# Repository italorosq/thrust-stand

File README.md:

# thrust-stand

## 📋 Sobre

Sistema embarcado baseado em ESP32 para monitoramento de testes estáticos de motores de foguetes, com aquisição de dados de empuxo e pressão em tempo real, armazenamento em cartão SD e comunicação via Serial/Bluetooth.

## 🚀 Quick Start

1. Clone o repositório

```bash
git clone https://github.com/ViniciusCMB/thrust-stand.git
```

2. Configure o hardware conforme [esquemático](./docs/HARDWARE.md)
3. Carregue o firmware

## 📁 Estrutura do Projeto

```
├── 📂 docs/              # Documentação técnica detalhada
├── 📂 extras/            # Códigos extras utilizados
├── 📂 firmware/          # Código do microcontrolador ESP32
├── 📂 hardware/          # Esquemáticos, PCBs e lista de componentes
├── 📂 software/          # Ferramentas de análise e interface
└── 📂 tests/             # Testes unitários e de integração
```

## 🔧 Pré-requisitos

- Hardware: ESP32 DevKit V1, célula de carga + HX711, sensor de pressão (com divisor resistivo), módulo microSD (SPI), 2 botões tácteis (`GPIO32` para TARE e `GPIO33` para novo arquivo), LED com resistor de limitação
- Software: Arduino IDE 2.0+
- Bibliotecas: ver `docs/FIRMWARE.md`

## 📖 Documentação

- [Esquemático e Montagem](./docs/HARDWARE.md)
- [Firmware e Arquitetura](./docs/FIRMWARE.md)
- [Protocolos e API](./docs/API.md)
- [Troubleshooting](./docs/TROUBLESHOOTING.md)

## 🎯 Funcionalidades

- ✅ Aquisição de dados de empuxo e pressão em tempo real
- ✅ Armazenamento em cartão SD com arquivos sequenciais
- ✅ Controle local por botões (TARE e novo arquivo)
- ✅ LED de status de gravação no SD
- ✅ Comunicação (Serial, Bluetooth)
- ✅ Calibração persistente da célula de carga

## 📊 Dados de Teste

Os dados de testes estáticos de motores específicos são armazenados no repositório dedicado:
[motor](https://github.com/Serra-Rocketry/motor)

Este repositório (thrust-stand) contém apenas o sistema de aquisição. Os dados coletados durante os testes devem ser commitados no repositório `motor`.

## 🤝 Contribuindo

Este projeto segue as [Boas Práticas da Serra Rocketry](https://github.com/Serra-Rocketry/best-practices). Para contribuir:

1. Fork o projeto
2. Crie uma branch para sua feature (`git checkout -b feature/AmazingFeature`)
3. Commit suas mudanças (`git commit -m 'Add some AmazingFeature'`)
4. Push para a branch (`git push origin feature/AmazingFeature`)
5. Abra um Pull Request

## ✨ Autores

- Equipe Serra Rocketry - Desenvolvimento e documentação
- Contribuidores - [Lista de contribuidores]()

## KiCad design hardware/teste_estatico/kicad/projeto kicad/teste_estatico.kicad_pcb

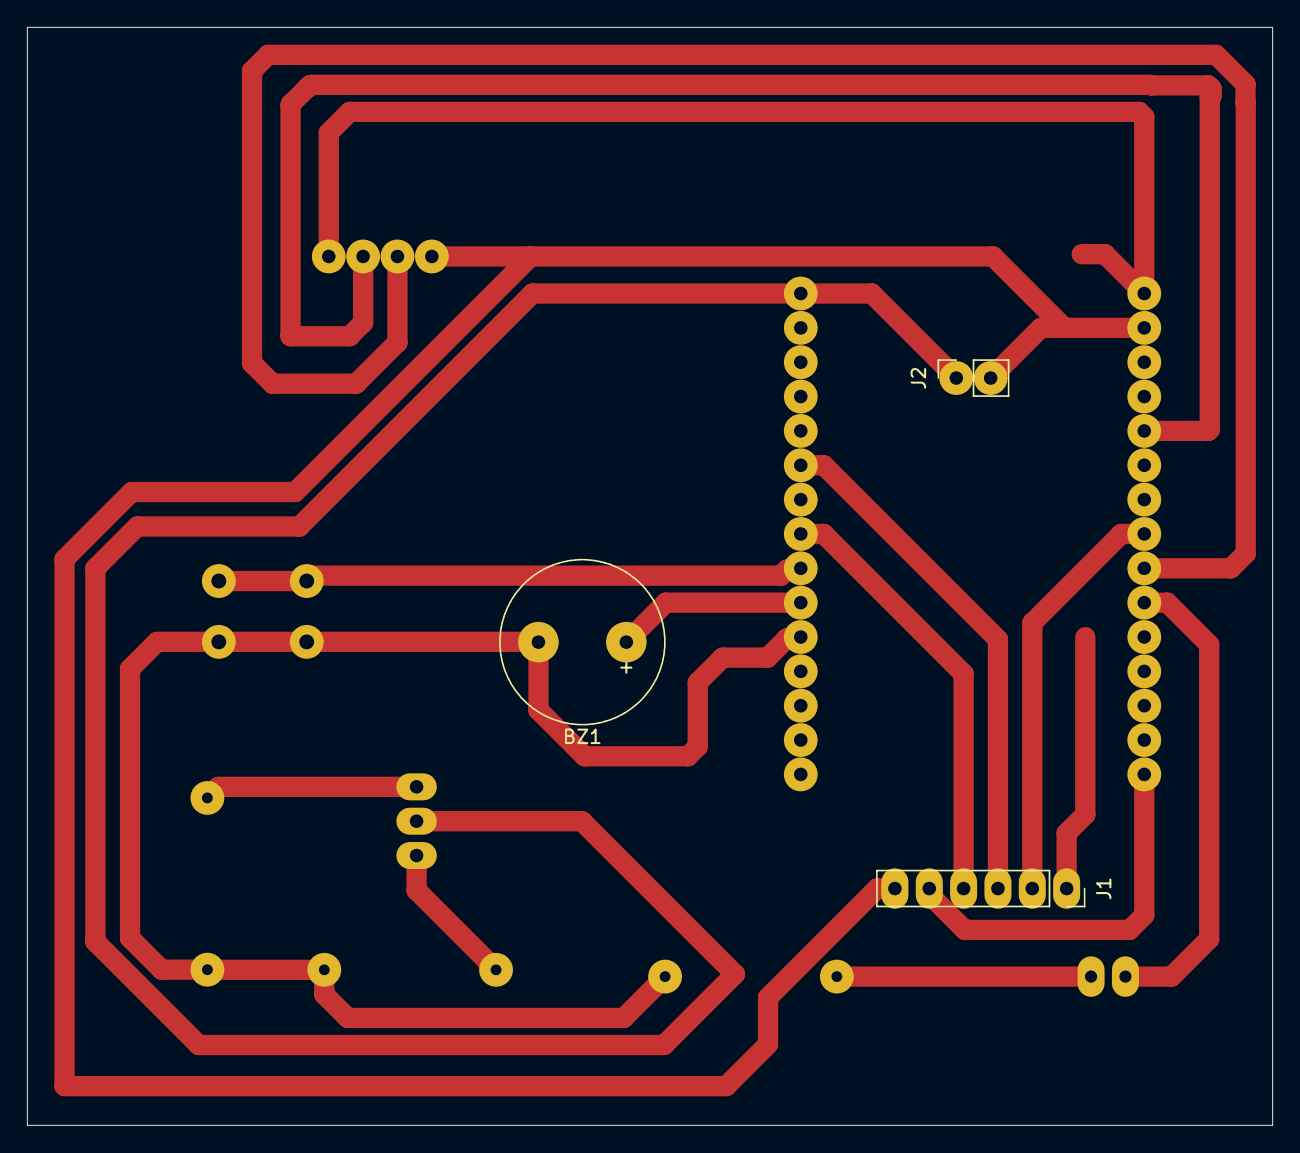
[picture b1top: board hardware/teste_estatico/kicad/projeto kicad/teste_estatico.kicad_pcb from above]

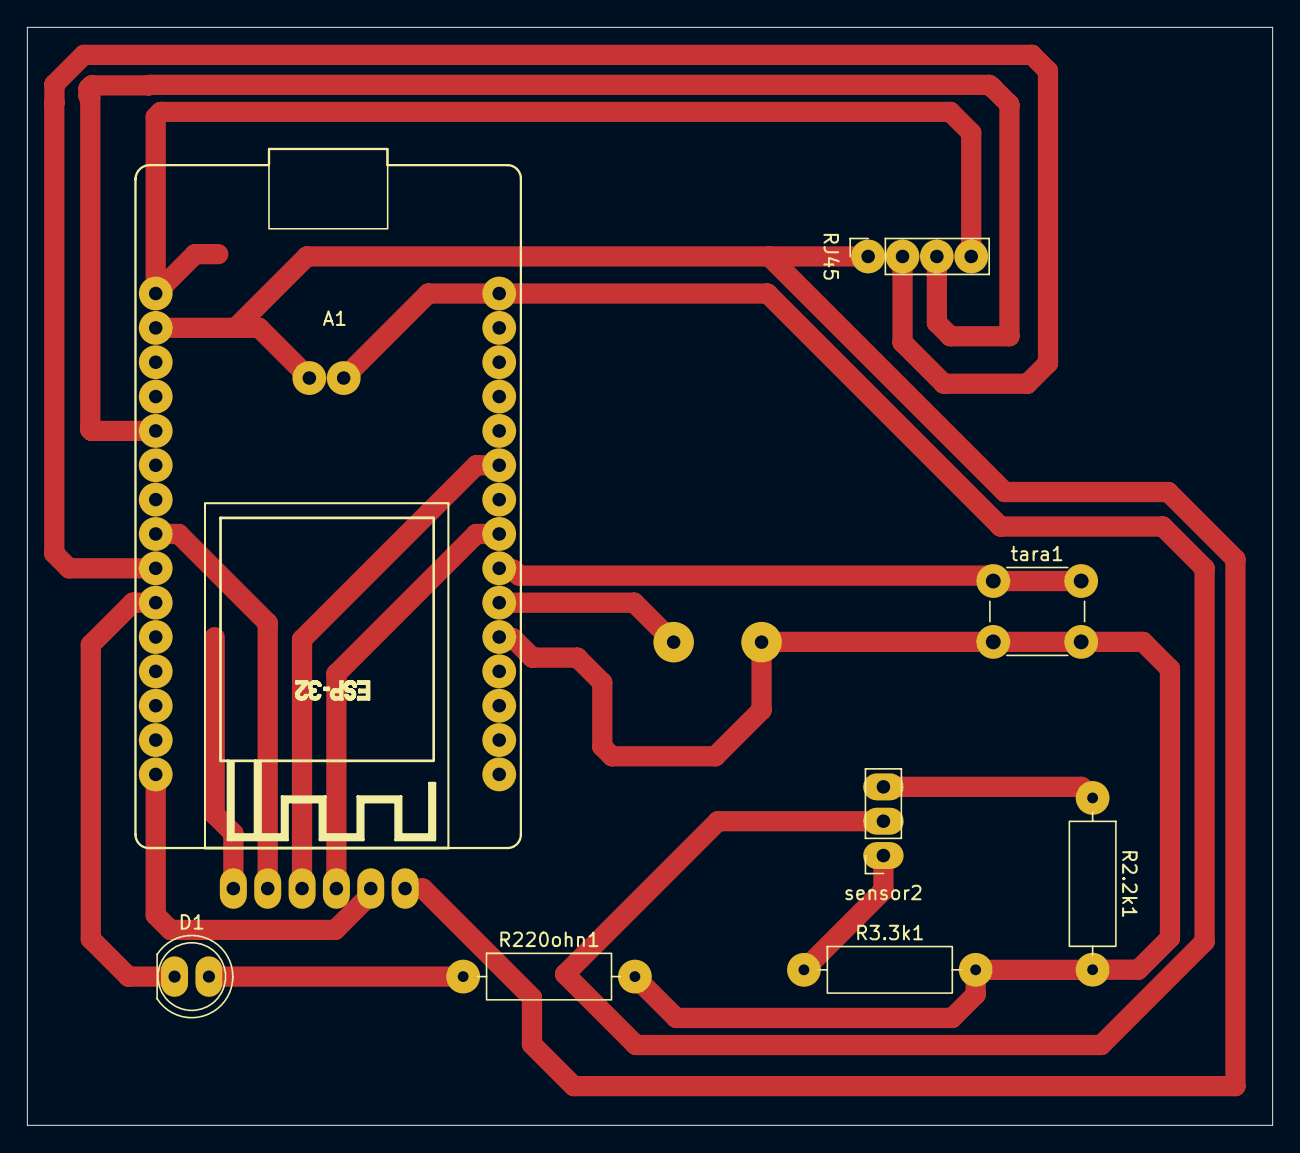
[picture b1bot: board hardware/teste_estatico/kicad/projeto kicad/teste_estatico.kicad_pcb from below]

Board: 2 copper layers, 92.1 x 81.2 mm, 11 parts (8 on the bottom side), 16 nets.

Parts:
A1: ESP32_DevKit_V1_DOIT_30GPIOs; DOIT_ESP32_DEVKIT_30Pins
BZ1: Buzzer_5V; MagneticBuzzer_ProSignal_ABT-410-RC
D1: LED; LED_D5.0mm_FlatTop
J1: PINHD_1x6_Female; PinSocket_1x06_P2.54mm_Vertical
J2: PINHD_1x2_Female; PinSocket_1x02_P2.54mm_Vertical
R2.2k1, R3.3k1, R220ohn1: R; R_Axial_DIN0309_L9.0mm_D3.2mm_P12.70mm_Horizontal
RJ45: conexão do rj45; PinSocket_1x04_P2.54mm_Vertical
sensor2: Sensor de pressão; PinSocket_1x03_P2.54mm_Vertical
tara1: Push_Button; SW_PUSH_6mm

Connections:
3.3V: A1.1 (3.3V), J1.1, RJ45.4
GND: A1.2 (GND), J1.6, J2.2, RJ45.1
unnamed: A1.21 (ADC1_CH4/D32), BZ1.1
unnamed: A1.22 (ADC1_CH4/D32), tara1.1
unnamed: A1.20 (ADC1_CH7/D35), A1.29 (GND), BZ1.2, R2.2k1.2, R3.3k1.2, R220ohn1.2, tara1.2
unnamed: A1.25 (ADC2_CH7/D27), J1.3
unnamed: A1.5 (D4/ADC2_CH0), RJ45.3
unnamed: A1.8 (D5), J1.2
unnamed: A1.9 (D18), RJ45.2
unnamed: A1.10 (D19), D1.1 (K)
unnamed: A1.15 (D23), J1.5
unnamed: A1.23 (DAC1/ADC2_CH8/D25), J1.4
unnamed: D1.2 (A), R220ohn1.1
unnamed: R2.2k1.1, sensor2.3
unnamed: R3.3k1.1, sensor2.1
VIN: A1.30 (VIN), J2.1, sensor2.2

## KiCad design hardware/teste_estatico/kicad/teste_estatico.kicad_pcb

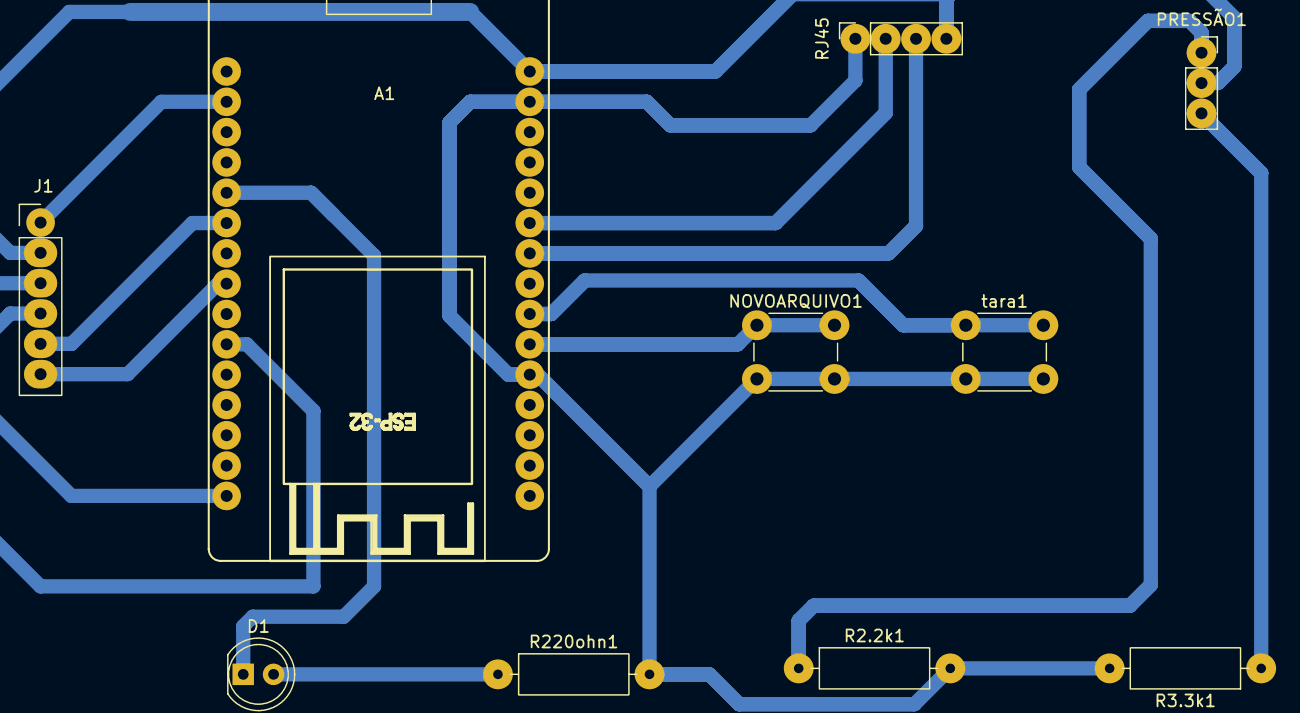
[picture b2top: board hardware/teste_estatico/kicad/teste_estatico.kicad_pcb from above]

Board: 2 copper layers, 10 parts (0 on the bottom side), 14 nets.

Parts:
A1: ESP32_DevKit_V1_DOIT_30GPIOs; DOIT_ESP32_DEVKIT_30Pins
D1: LED; LED_D5.0mm_FlatTop
J1: PINHD_1x6_Female; PinSocket_1x06_P2.54mm_Vertical
NOVOARQUIVO1: Push_Button; SW_PUSH_6mm
PRESSÃO1: Sensor de pressão; PinSocket_1x03_P2.54mm_Vertical
R2.2k1, R3.3k1, R220ohn1: R; R_Axial_DIN0309_L9.0mm_D3.2mm_P12.70mm_Horizontal
RJ45: conexão do rj45; PinSocket_1x04_P2.54mm_Vertical
tara1: Push_Button; SW_PUSH_6mm

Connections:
unnamed: A1.21 (ADC1_CH4/D32), NOVOARQUIVO1.1
unnamed: A1.22 (ADC1_CH4/D32), tara1.1
unnamed: A1.20 (ADC1_CH7/D35), A1.29 (GND), NOVOARQUIVO1.2, R2.2k1.2, R3.3k1.2, R220ohn1.2, RJ45.1, tara1.2
unnamed: A1.25 (ADC2_CH7/D27), RJ45.2
unnamed: A1.5 (D4/ADC2_CH0), D1.1 (K)
unnamed: A1.8 (D5), J1.6
unnamed: A1.10 (D19), J1.3
unnamed: A1.15 (D23), J1.4
unnamed: A1.24 (DAC2/ADC2_CH9/D26), RJ45.3
unnamed: A1.2 (GND), J1.1
unnamed: A1.6 (RX2/GPIO16), J1.5
unnamed: A1.30 (VIN), J1.2, PRESSÃO1.2, RJ45.4
unnamed: D1.2 (A), R220ohn1.1
unnamed: PRESSÃO1.1, R2.2k1.1

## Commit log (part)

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2026-05-08 Docs: align documentation with updated schematic controls
2026-05-08 add imagem do esquematico atualizado
2026-05-11 adcionado arquivo para fabricação cnc
2026-05-11 adcionado atulização nos arquivos de pcb kicad
2026-05-14 atulização nos arquivos de pcb
2026-05-16 Atualiza ponteiro do histórico KiCad
2026-05-16 Adiciona arquivo PCB do teste estatico
2026-05-29 feat: adcionado arquivos de fabricação e modificação na pcb
